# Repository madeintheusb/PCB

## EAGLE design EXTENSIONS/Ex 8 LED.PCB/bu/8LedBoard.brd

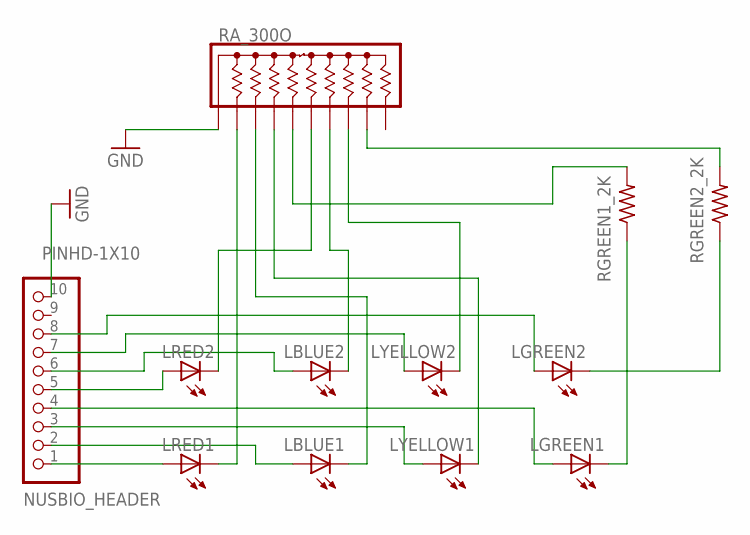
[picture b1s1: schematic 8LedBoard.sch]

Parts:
LBLUE1, LBLUE2: LED5MM
LGREEN1, LGREEN2: LED5MM
LRED1, LRED2: LED5MM
LYELLOW1, LYELLOW2: LED5MM
NUSBIO_HEADER: PINHD-1X10; 1X10-BIG
RA_300O: 4610X; SIP10
RGREEN1_2K, RGREEN2_2K: R-US_0207/10; 0207/10

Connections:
GND: NUSBIO_HEADER.10, RA_300O.1
unnamed: LGREEN2.A, NUSBIO_HEADER.8
unnamed: LRED1.A, NUSBIO_HEADER.1
unnamed: LBLUE1.A, NUSBIO_HEADER.2
unnamed: LYELLOW1.A, NUSBIO_HEADER.3
unnamed: LGREEN1.A, NUSBIO_HEADER.4
unnamed: LRED2.A, NUSBIO_HEADER.5
unnamed: LBLUE2.A, NUSBIO_HEADER.6
unnamed: LYELLOW2.A, NUSBIO_HEADER.7
unnamed: LRED1.K (C), RA_300O.2
unnamed: LBLUE1.K (C), RA_300O.3
unnamed: LYELLOW1.K (C), RA_300O.4
unnamed: LRED2.K (C), RA_300O.6
unnamed: LBLUE2.K (C), RA_300O.7
unnamed: LYELLOW2.K (C), RA_300O.8
unnamed: LGREEN1.K (C), RGREEN1_2K.1
unnamed: RA_300O.5, RGREEN1_2K.2
unnamed: LGREEN2.K (C), RGREEN2_2K.1
unnamed: RA_300O.9, RGREEN2_2K.2

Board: 2 copper layers, 12 parts (0 on the bottom side), 19 nets, no tracks yet.

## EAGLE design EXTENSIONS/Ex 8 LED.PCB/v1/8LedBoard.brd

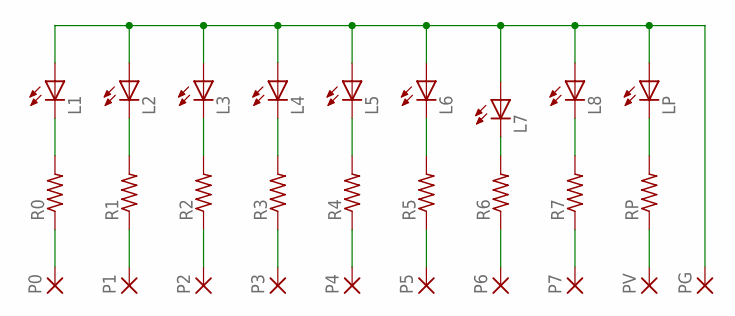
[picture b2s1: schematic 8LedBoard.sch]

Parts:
L1, L2, L3, L4, L5, L6, L7, L8: LED5MM
LP: LED5MM
P0, P1, P2, P3, P4, P5, P6, P7: 1,6/0,9
PG: 1,6/0,9
PV: 1,6/0,9
R0, R1, R2, R3, R4, R5, R6, R7: R-US_0207/10; 0207/10
RP: R-US_0207/10; 0207/10

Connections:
L3: L3.K (C), R2.2
unnamed: P0.1, R0.1
unnamed: P1.1, R1.1
unnamed: P2.1, R2.1
unnamed: L5.K (C), R4.2
unnamed: P3.1, R3.1
unnamed: L6.K (C), R5.2
unnamed: P4.1, R4.1
unnamed: L8.K (C), R7.2
unnamed: L1.K (C), R0.2
unnamed: L2.K (C), R1.2
unnamed: P5.1, R5.1
unnamed: L4.K (C), R3.2
unnamed: L7.K (C), R6.2
unnamed: P6.1, R6.1
unnamed: P7.1, R7.1
unnamed: PV.1, RP.1
unnamed: L1.A, L2.A, L3.A, L4.A, L5.A, L6.A, L7.A, L8.A, LP.A, PG.1
unnamed: LP.K (C), RP.2

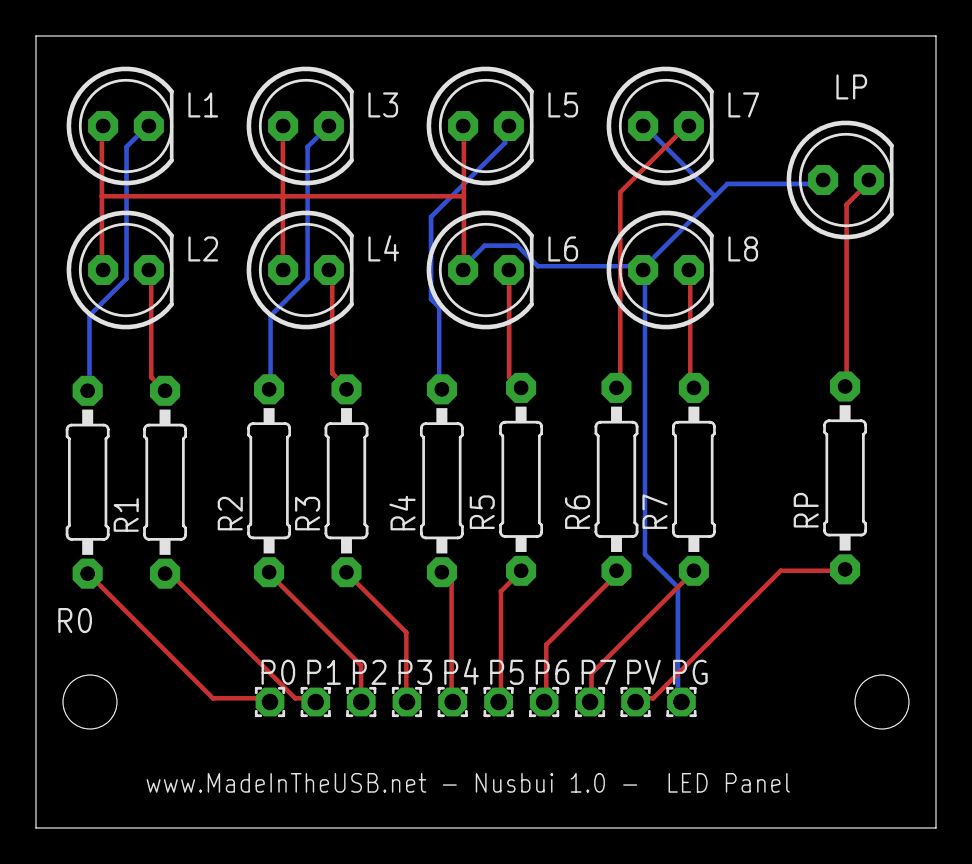
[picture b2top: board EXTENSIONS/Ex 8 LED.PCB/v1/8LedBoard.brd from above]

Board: 2 copper layers, 50.0 x 44.0 mm, 28 parts (0 on the bottom side), 19 nets.

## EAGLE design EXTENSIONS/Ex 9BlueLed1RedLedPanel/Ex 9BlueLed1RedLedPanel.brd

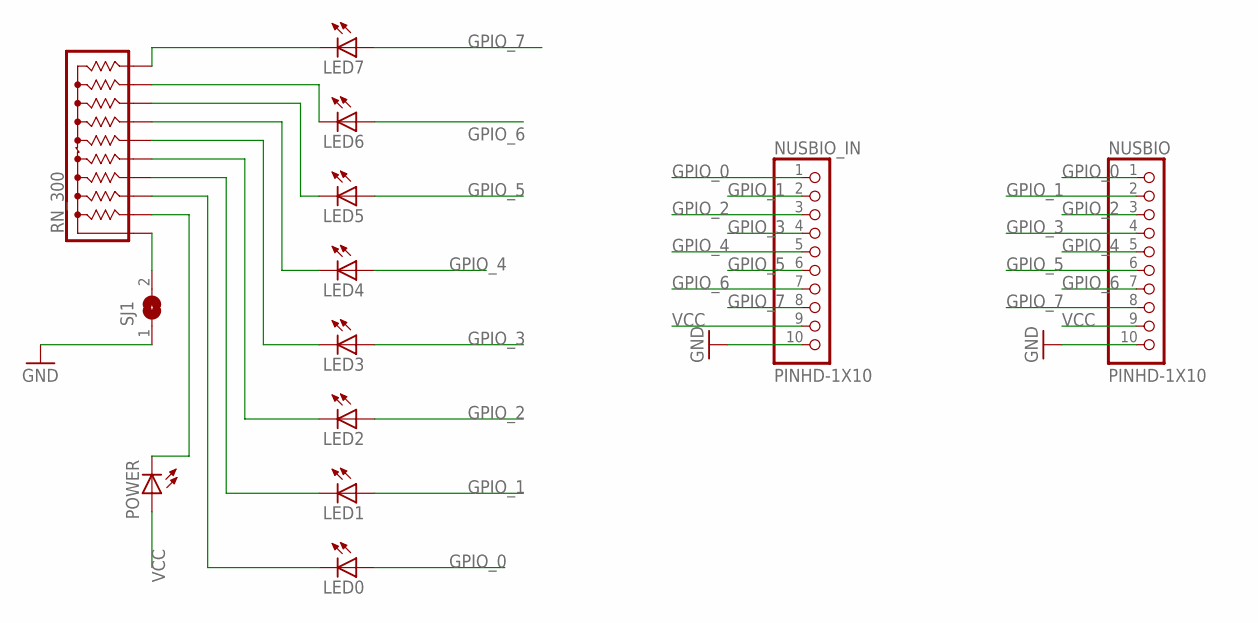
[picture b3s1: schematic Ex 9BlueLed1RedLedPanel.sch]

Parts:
LED0, LED1, LED2, LED3, LED4, LED5, LED6, LED7: LEDSMT1206; 1206
NUSBIO: PINHD-1X10; 1X10-BIG
NUSBIO_IN: PINHD-1X10; 1X10-BIG
POWER: LEDSMT1206; 1206
RN_300: 4610X; SIP10
SJ1: SOLDERJUMPERREFLOW_NOPASTE; SOLDERJUMPER_REFLOW_NOPASTE

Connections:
GND: NUSBIO.10, NUSBIO_IN.10, SJ1.1
GPIO_0: LED0.A, NUSBIO.1, NUSBIO_IN.1
GPIO_1: LED1.A, NUSBIO.2, NUSBIO_IN.2
GPIO_2: LED2.A, NUSBIO.3, NUSBIO_IN.3
GPIO_3: LED3.A, NUSBIO.4, NUSBIO_IN.4
GPIO_4: LED4.A, NUSBIO.5, NUSBIO_IN.5
GPIO_5: LED5.A, NUSBIO.6, NUSBIO_IN.6
GPIO_6: LED6.A, NUSBIO.7, NUSBIO_IN.7
GPIO_7: LED7.A, NUSBIO.8, NUSBIO_IN.8
unnamed: POWER.C, RN_300.2
unnamed: RN_300.1, SJ1.2
unnamed: LED7.C, RN_300.10
unnamed: LED6.C, RN_300.9
unnamed: LED5.C, RN_300.8
unnamed: LED4.C, RN_300.7
unnamed: LED3.C, RN_300.6
unnamed: LED2.C, RN_300.5
unnamed: LED1.C, RN_300.4
unnamed: LED0.C, RN_300.3
VCC: NUSBIO.9, NUSBIO_IN.9, POWER.A

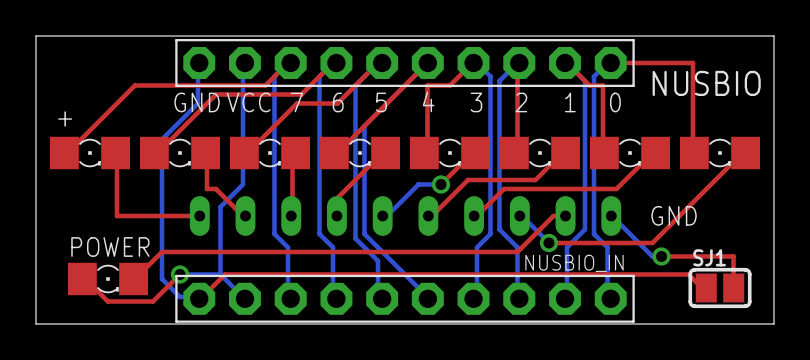
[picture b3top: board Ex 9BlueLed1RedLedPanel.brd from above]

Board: 2 copper layers, 41.0 x 16.0 mm, 13 parts (1 on the bottom side), 20 nets.

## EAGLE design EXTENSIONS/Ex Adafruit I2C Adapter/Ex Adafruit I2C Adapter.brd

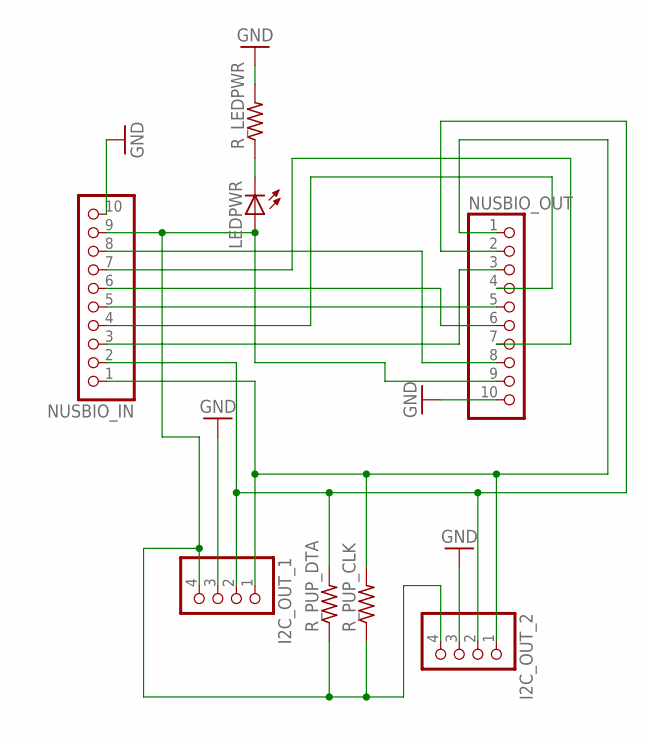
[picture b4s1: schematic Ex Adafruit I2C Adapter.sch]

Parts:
I2C_OUT_1, I2C_OUT_2: PINHD-1X4; 1X04
LEDPWR: LEDCHIPLED_0805; CHIPLED_0805
NUSBIO_IN: PINHD-1X10; 1X10-BIG
NUSBIO_OUT: PINHD-1X10; 1X10-BIG
R_LEDPWR: R-US_R0805; R0805
R_PUP_CLK: R-US_R0805; R0805
R_PUP_DTA: R-US_R0805; R0805

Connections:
GND: I2C_OUT_1.3, I2C_OUT_2.3, NUSBIO_IN.10, NUSBIO_OUT.10, R_LEDPWR.2
unnamed: LEDPWR.C, R_LEDPWR.1
unnamed: I2C_OUT_1.4, I2C_OUT_2.4, LEDPWR.A, NUSBIO_IN.9, NUSBIO_OUT.9, R_PUP_CLK.1, R_PUP_DTA.1
unnamed: NUSBIO_IN.6, NUSBIO_OUT.6
unnamed: NUSBIO_IN.5, NUSBIO_OUT.5
unnamed: NUSBIO_IN.3, NUSBIO_OUT.3
unnamed: NUSBIO_IN.8, NUSBIO_OUT.8
unnamed: NUSBIO_IN.4, NUSBIO_OUT.4
unnamed: NUSBIO_IN.7, NUSBIO_OUT.7
unnamed: I2C_OUT_1.1, I2C_OUT_2.1, NUSBIO_IN.1, NUSBIO_OUT.1, R_PUP_CLK.2
unnamed: I2C_OUT_1.2, I2C_OUT_2.2, NUSBIO_IN.2, NUSBIO_OUT.2, R_PUP_DTA.2

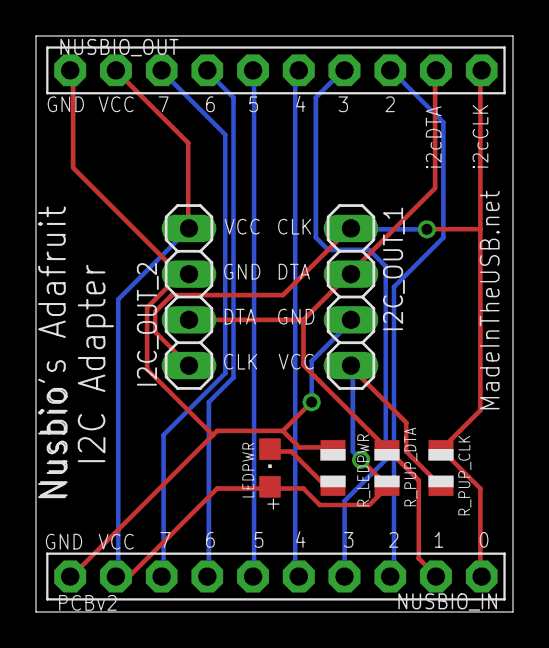
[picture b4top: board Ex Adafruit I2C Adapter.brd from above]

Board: 2 copper layers, 26.5 x 32.0 mm, 8 parts (0 on the bottom side), 11 nets.

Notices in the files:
parts and their libraries:
microbuilder: This work is placed in the public domain, and may be freely used for commercial and non-commercial work with the following conditions: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
SparkFun-Aesthetics: Licensing: Creative Commons ShareAlike 4.0 International - https://creativecommons.org/licenses/by-sa/4.0
